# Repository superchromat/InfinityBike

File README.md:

# Infinity Bike

Welcome to the Infinity Bike repository. A simple and inexpensive indoors bike training video game with built-in sensors that allows the player to ride on a virtual track.

Visit our website! www.infinitybike.net

## Why use Infinity Bike? 

Rainy days and the Winter season can really disrupt a training program. Riders always have the option to mount their bike on a trainer but the monotony of trainers
will always make it a bit difficult to keep up the pace. This is why we decided to add a little bit on interactivity to our training program. The Infinity Bike set-up is designed to be a simple as possible
while still allowing a rider to read the speed and steering from a bike mounted on any trainers and relay the information to the computer. 

See the Youtube video (for a deprecated version of Infinity Bike): 

## Where are we in development 
In its current form, the code should compile on a Windows or Mac. We have the communication between Arduino and Unity established and we even have a demo track that you can use to test
your set-up. If you want to take full advantage of this work, you will need to have access to a 3D printer. (Tip : A lot of community libraries are starting to have them available to the public.)
Alternatively, you could design and machine your own parts. If you do, let us know!

## Installation
To participate to this project, start by cloning the repository to a drive on your computer. You should get all the assets for the Unity program in the Infinity Bike folder and the Arduino Code in the ArduiBike folder.
Don't have a bike/trainer or access to a 3D printer? You can easily build a small arduino circuit that fits on your desk. Alternatively, the Arduino inputs can be emulated with the keyboard by
setting a flag in the Unity inspector.

If you make a change you think is worth including in the main project, send us a pull request and we will review it! 

Sadly, we don't have a ready out of the box version yet but it's on the to-do list. For now, you will need to clone the repository and build the current scene for your system.
### Hardware
#### Non 3D Printed parts list

1 x <a href="https://store.arduino.cc/usa/arduino-nano">Arduino nano</a> ($22.00)<br/>
1 x <a href="https://www.amazon.com/Elegoo-6PCS-tie-points-Breadboard-Arduino/dp/B01EV6SBXQ/ref=br_lf_m_d2xh2ecztuwj4fa_img?_encoding=UTF8&s=pc">Mini Breadboard</a> ($1.33/unit)<br/>
1 x <a href="https://www.aliexpress.com/item/100PCS-LOT-1-4W-220-ohm-resistor-1-ROHS1-4w-220R-ohm-Metal-Film-Resistors/32689231347.html?spm=2114.search0104.3.22.6e6347b5Z7ERSI&ws_ab_test=searchweb0_0,searchweb201602_2_10152_10065_10151_10344_10068_10130_5722815_10342_10547_10343_10340_5722915_10548_10341_5722615_10696_10084_10083_10618_10139_10307_5722715_5711215_10059_308_100031_10103_10624_10623_10622_5711315_5722515_10621_10620,searchweb201603_1,ppcSwitch_5&algo_expid=38f3e0b1-dc13-4f86-8131-47538c0df9db-3&algo_pvid=38f3e0b1-dc13-4f86-8131-47538c0df9db&priceBeautifyAB=0">220 Ohm resistor</a> ($1.00/kit)<br/>
1 x <a href="https://www.amazon.com/Uxcell-a15011600ux0235-Linear-Rotary-Potentiometer/dp/B01DKCUVMQ/ref=zg_bs_306810011_1?_encoding=UTF8&psc=1&refRID=ZPQ3XYHZQJXNW7W0AH5P">10K Potentiometer </a> ($1.80/unit)<br/>
1 x <a href="https://www.aliexpress.com/item/KY-003-Standard-Hall-Magnetic-Sensor-Module-Works-with-Arduino-Boards-for-Arduino/32693432353.html?spm=2114.search0104.3.186.599d770dWMU1Zt&ws_ab_test=searchweb0_0,searchweb201602_2_10152_10065_10151_10344_10068_10130_5722815_10342_10547_10343_10340_5722915_10548_10341_5722615_10696_10084_10083_10618_10139_10307_5722715_5711215_10059_308_100031_10103_10624_10623_10622_5711315_5722515_10621_10620,searchweb201603_1,ppcSwitch_5&algo_expid=5d7e9e2e-c6de-4431-8a5b-cecc73fa021c-27&algo_pvid=5d7e9e2e-c6de-4431-8a5b-cecc73fa021c&priceBeautifyAB=0">Hall sensor </a> ($0.96)<br/>
20 cm x <a href="https://www.aliexpress.com/item/5m-lot-GT2-6mm-open-timing-belt-width-6mm-GT2-belt-Rubbr-Fiberglass-cut-to-length/32811832945.html?spm=2114.search0104.3.50.4ca843e4JrNX47&ws_ab_test=searchweb0_0,searchweb201602_2_10152_10065_10151_10344_10068_10130_5722815_10342_10547_10343_10340_5722915_10548_10341_5722615_10696_10084_10083_10618_10139_10307_5722715_5711215_10059_308_100031_10103_10624_10623_10622_5711315_5722515_10621_10620,searchweb201603_1,ppcSwitch_5&algo_expid=1aae0170-0588-45a1-a4ac-2558d64e76cf-7&algo_pvid=1aae0170-0588-45a1-a4ac-2558d64e76cf&priceBeautifyAB=0"> 6 mm 3D printer timing belt </a> ($3.33)<br>
1 kit x <a href="https://www.aliexpress.com/item/Hot-Sale-1-Set-300pcs-M3-304-Stainless-Steel-Hex-Socket-Screws-Bolt-With-Hex-Nuts/32808686142.html?spm=2114.search0104.3.1.703b7491nfv8lT&ws_ab_test=searchweb0_0,searchweb201602_2_10152_10065_10151_10344_10068_10130_5722815_10342_10547_10343_10340_5722915_10548_10341_5722615_10696_10084_10083_10618_10139_10307_5722715_5711215_10059_308_100031_10103_10624_10623_10622_5711315_5722515_10621_10620,searchweb201603_1,ppcSwitch_5&algo_expid=671cbcd2-b8c1-400f-b5f3-cc37f87cfeda-0&algo_pvid=671cbcd2-b8c1-400f-b5f3-cc37f87cfeda&priceBeautifyAB=0">Various Lenght M3 screws and bolts</a> ($6.82)<br/>
1 x <a href= "https://www.aliexpress.com/item/Universal-Magnet-For-Bicycle-Bike-Cycling-Computer-Works-Speedometer-Odometer-Drop-Shipping/32852306956.html?spm=2114.search0104.3.21.32461d8aw5yTQN&ws_ab_test=searchweb0_0,searchweb201602_2_10152_10065_10151_10344_10068_10130_5722815_10342_10547_10343_10340_5722915_10548_10341_5722615_10696_10084_10083_10618_10139_10307_5722715_5711215_10059_308_100031_10103_10624_10623_10622_5711315_5722515_10621_10620,searchweb201603_1,ppcSwitch_5&algo_expid=20a02fd9-cbb1-4fab-92b5-93c50623b4ab-3&algo_pvid=20a02fd9-cbb1-4fab-92b5-93c50623b4ab&priceBeautifyAB=0"> Bicycle speedometer magnet </a> ($0.98) <br/>

** Estimated prices

#### 3D Printed parts list
All the 3D print .stl files are available on [Thingiverse](https://www.thingiverse.com/thing:2933374). The picture below list them all. 
We mounted the material above with 3D printed parts. 
The files we used are listed bellow and they're numbered with the same convention as the image above. 
You can use them as-is but make sure that the dimensions we used match your bike.

##### Parts filename
1. FrameConnection_PotentiometerHolder_U_Holder.stl
2. FrameConnection_Spacer.stl
3. BreadboardFrameHolder.stl
4. Pulley_PotentiometerSide.stl
5. Pot_PulleyConnection.stl
6. FrameConnection.stl
7. Pulley_HandleBarSide_Print2.stl
8. FrameToHallSensorConnector.stl
9. PotHolder.stl
10. HallSensorAttach.stl
##### Assembled parts pictures

Please note that we are currently working on a better stearing measurement device. As seen in the picture above, it is based on a rotation platform placed under the bike wheel. 

More info on this device is available [here](https://github.com/AlexandreDoucet/InfinityBike/tree/master/Ressources/3DprintedParts%20STL%20V0.1/RotationPlatform).

#### Circuit

## How to use?
We published a short 
<a href="https://www.instructables.com/id/Infinity-Bike-Indoors-Bike-Training-Video-Game/">instructable</a> 
tutorial that should provide enough information to get started with this project. 

Please note that this tutorial is no longer up to date with the project and will need to be revisited. Building a more in-depth tutorial for potential contributors is on our To-do list.

** Because we used blender to generate the 3d models, you must have blender installed before opening the project. Otherwise some assets wont load properly.**

## How to contribute? 
From now on, we use the [git branching model proposed by Vincent Driessen](https://nvie.com/posts/a-successful-git-branching-model/). 

To add features to the project, please branch out of the develop branch. The testing of pull request will be done with the 018.3.12f1 version of Unity. 

### Project structure 

### Medium term goals 

## Credits
### Project contributors
Alexandre Doucet (_Doucet_)</br>
Maxime Boudreau (MxBoud)</br>
Alexis Nosovich 

### External ressources
[The Unity game engine](https://unity3d.com)

This project started after we read the tutorial by Allan Zucconi "how to integrate Arduino with Unity" ( https://www.alanzucconi.com/2015/10/07/how-to-integrate-arduino-with-unity/ )

The request from the Arduino are handled using the SerialCommand library ( https://github.com/kroimon/Arduino-SerialCommand )

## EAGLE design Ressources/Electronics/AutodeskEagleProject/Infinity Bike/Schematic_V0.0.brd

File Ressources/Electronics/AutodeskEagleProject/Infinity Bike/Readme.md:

This is the first iteration of a custom PCB for the Infinity bike project.

It has been tested and it works, but some improvement are planned for the next iteration:

-The holes on the PCB are systematically too small.
-We will design places for a few buttons. The main purpose of these buttons would be to enable an in game calibration sequence to make sure the steering behaves as expected.
-The design needs some mounting holes.
-The spacing between the JST connectors needs to be increased.

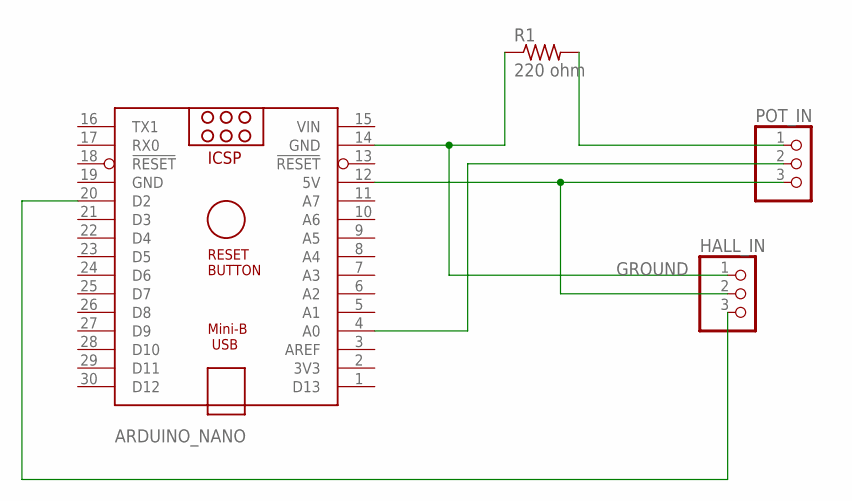
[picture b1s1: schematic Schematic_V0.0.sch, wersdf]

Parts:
ARDUINO_NANO: ARDUINO_NANO
HALL_IN: PINHD-1X3; 1X03
POT_IN: PINHD-1X3; 1X03
R1: 220 ohm; 0204/7

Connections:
GROUND: ARDUINO_NANO.14 (GND), ARDUINO_NANO.19 (GND), HALL_IN.1, R1.1
unnamed: ARDUINO_NANO.12 (5V), HALL_IN.2, POT_IN.3
unnamed: POT_IN.1, R1.2
unnamed: ARDUINO_NANO.4 (A0), POT_IN.2
unnamed: ARDUINO_NANO.20 (D2), HALL_IN.3
VIN: ARDUINO_NANO.15 (VIN)

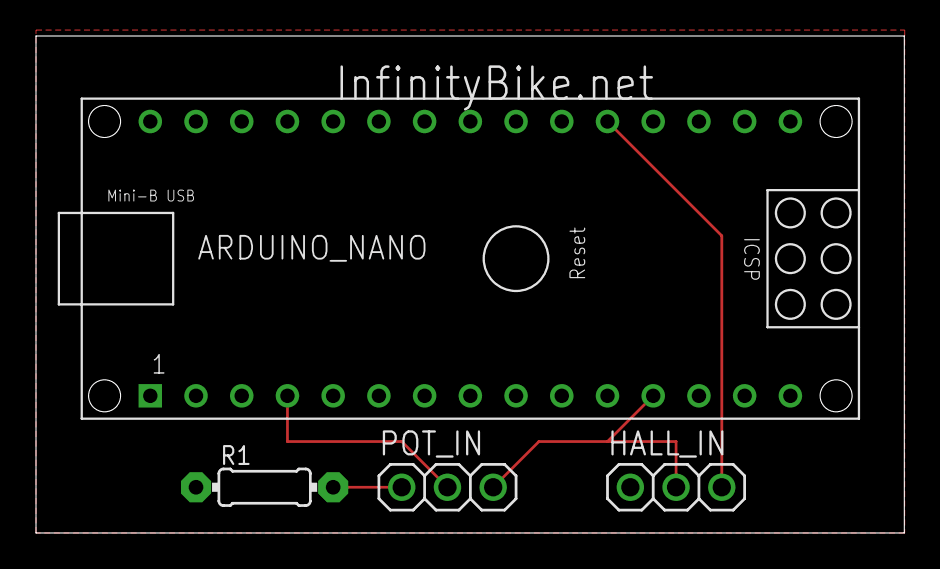
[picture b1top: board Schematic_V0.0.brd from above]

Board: 2 copper layers, 48.2 x 27.6 mm, 4 parts (0 on the bottom side), 5 nets.

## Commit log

2018-05-25 Clean Up
2018-05-25 Initial Unity Commit
2018-05-25 Adding the Unity and Arduino Files
2018-05-25 Unity Assets
2018-05-25 Extra instructable info
2018-05-25 Additionnal Unity Settings
2018-05-26 Added a port auto detection to start communication with the arduino without having to select the comport manually.
2018-05-27 Marginal changes
2018-05-27 Fixed a small bug in SerialCommand.cpp
2018-05-27 Updated ArduinoThread so the AutoDetect works also on macOs
2018-05-27 changes to the README
2018-05-27 Scene cleanups and added a read me.
2018-05-27 Read Me Typos
2018-05-27 Added the logo image
2018-05-27 Updated Logo
2018-05-27 Minor changes
2018-05-27 Minor changes to the Read me.
2018-05-27 Added circuit schematics
2018-05-27 Added Hardware list to ReadMe
2018-05-27 Added some images
2018-05-27 Added the assembled parts picture
2018-05-27 Minor tweaks
2018-05-27 Added instructable hyperlink
2018-05-30 Cleaned up the folders and modified the Respawned tools.
2018-05-31 Tweaked the behaviour of the camera.
2018-06-01 Improved on the bike physics.
2018-06-01 Removed objects from scene that required a prefab to test a missing prefab problem.
2018-06-01 .' git commit -m. git commit -m".
2018-06-02 1. added "NPCs" that spawn on the track and travel with the player. Their speed was set up to match closely the current speed of the player with some added variations to make it feel a bit more natur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
2018-06-03 General clean up of the project folders. Added a few safegards to the EditorRespawNodeSet script to prevent errors is no track node array is selected.
2018-06-03 Added a public variable to change the distance the NPC spawns bebehind the player.
2018-06-03 Fixed a bug where the respawning NPC spawned outside of the track.
2018-06-03 Tweaked the friction on the player to make slowing down smoother.
2018-06-04 Added FOV variability with the speed to improve the feeling of speed.
2018-06-05 prevented spawning ahead of the player by preventing spawning of slower npc.
2018-06-06 Fixed the arduino not connecting but when changing ports, the arduino code must be re uploaded.
2018-06-10 Fixed Arduino Thread so it works if useArduinoPort = false.
2018-06-12 Fixed the auto detect function to properly detect arduino. Added the option to plug, unplug and replug arduino while code is active.
2018-06-13 Refactoring of the arduino thread and player controler.
2018-06-13 Started implementing a level select menue.
2018-06-14 Added new elements and scripts to the start screen to select a button by accelerating on the bike. This should allow the play to navigate menues using only the front wheel angle and the speed of the 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
2018-06-14 Added transparent BG logo
2018-06-15 Added a few tweaks to the arduino code to make the transition between UNO and Nano smoother.
    Changed how the main screen detected the buttons to make it automatic.
    Added an exit application button to the main screen.
2018-06-17 Fixed the main screen softlock if you entered the options menu.
2018-06-18 Implemented self driving AI
2018-06-18 Added a save/load system to the AiSettings.
2018-06-20 added variable AI player
2018-06-20 Made improvements on the track node tools but accidently deleted all the existing nodes :)
2018-06-20 Regenerated the track nodes
2018-06-21 Tweaked the npc initial conditions and player data.
2018-06-22 Fixed track nodes and improve node setting tool
2018-06-22 Added a save/load to the track nodes
2018-07-02 Made significant refactoring to the Arduino Code and eliminated the need to create a new thread thread every time Unity makes a request.
    Added a windows paint startscreen because art is hard.
2018-07-02 You can now navigate the menus. There is still lots of refactoring to do but it's functionnal.
2018-07-02 Added keyboard controls
2018-07-02 Added TerrainBuilderTools
2018-07-02 Updated terrain
2018-07-03 Tweaked the bike physics to reduce gitterness
2018-07-05 Changed the layout and bugproofed the tracknode tool. Added a PID calculation to the AI drivers to help them when they get stuck on a hill.
2018-07-06 Tweaked physics on the bike to try and minimise the rough ride. Improved the loading/saving to display the available tracks in the editor.
2018-07-10 Added more error handling for the arduino thread
2018-07-15 Tweaked the camera to smooth jitter when riding on rough terrain.
2018-07-15 Added keyboard controls via the run arduino thread script.
2018-07-16 Added a respawn option to the menu in the main game.
2018-07-16 Added terrain builder tools prototype.
2018-07-17 Fixed UV maping and added a test track.
2018-07-18 Grammar and typos
    Fixed some grammar errors and typos.
2018-07-18 Added an example of how to use BezierSpline.
2018-07-18 Improved TerrainBuilderTools and created the first loop track with bezier curve...and treesgit add .
2018-07-20 Added Trees (TO MANY OF THEMgit add . )
2018-07-20 Added a loading screen and tweaked the menu system/layout.
2018-07-20 Fixed a merge conflict in the MainGame2 scene
2018-07-23 Added a new texture
2018-07-23 Added a new experimental terrain.
2018-07-26 Improved UI functionalitied and it looks nicer now.
2018-07-27 - Added a save/load feature to the besier spline script. You can access these with a right click on the script in the inspector. - "Fixed" the mesh having a gap at the start when the loop is closed. 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
2018-07-27 Investigated and resolve the bezier points disappearing.
2018-07-27 Adde a temporary soothing to the track so allow testing on it. Currently averages track heights over a few spots in the MeshfromSpline script
2018-08-01 -Made adjustements and fixed to the save/load scripts. -Changed the way the track node tool generates the nodes from the bezier curve. -Fixed the AI drivers to allow for much closer track nodes witho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
2018-08-03 Rearanged folders to allow the project to be build.
2018-08-03 Added the ability to draft behind NPC for a reduced wind resistance.
2018-08-03 AiDriver Optimisations
2018-08-03 Improved performance by refactoring AiDriver and respawn code
2018-08-04 Improved terrain
2018-08-04 Fixed discontinuity at the end of a track loop
2018-08-04 Fixed track discontinuity
2018-08-04 Tweaked the AI driver script
2018-08-04 Made minor fixes to the 3DPlayer Idle state
2018-08-04 Adjusted some features of the MountainViewMap
2018-08-04 Improved AI, AI generator and AI respawning
2018-08-04 Fixed more merge conflicts
2018-08-04 Fixed the velocity not displaying
2018-08-05 Refactored the code for drafting to allow a more modularity with it.
2018-08-05 Updated the current build
2018-08-06 Fixed respawn button not being linked to the player resspawns script.
2018-08-06 Removed duplicate function that called and subscribed to the onRespawn actions
2018-08-07 Simplified the references in the canvas to the player rigidbody by adding a the commonCanvasVariables script to the canvas
2018-08-09 Improved AI performance/spawning scenarios.
2018-08-10 - Improved the AI PID with scripted PID tuner. - Changed drafting mechanics to let the AI match the speed of the player drafting to allow for longer drafting sessions.
2018-08-10 Updated current build
2018-08-10 minor updates to PID values
2018-08-17 Tweaked NPC behaviour to keep the spawning around the player.
2018-10-22 Updated a few scripts and names
2018-10-27 Added the a particule system to the drafting target
2018-11-10 Worked on the 3D models
2018-11-10 Fixed merge conflict
2018-12-16 Implemented a graph system in the game.
2018-12-16 Tweaked when the data should be collected for the graph.
2018-12-30 Improved the cyclist 3d Model
2018-12-30 Added the hidden mac file to .gitignore
2019-01-02 In the process of implementing the 3d model in the main scene.
2019-01-02 Improved the animated cyclist prefab
2019-01-14 Added V0.1 of the rotation detection model.
2019-01-14 Repaired broken link
2019-01-15 adding 3d model on npc
2019-01-15 Improved cyclist animation
2019-01-15 Fixed a wierd but where unity wouln'd link the NPC wheels to the correct entity.
2019-01-17 Fixed a few errors that appeared when the new graphic assets werre added with the mountain view scene. - Also fixed error with the power graph.
2019-01-31 Fixed the menues not appearing properly and the graphs not stoping properly
2019-01-31 Correcting changes that didn't save properly.
2019-01-31 Fixed the data aquisition happening when the player is not moving at the start of the run.
2019-03-31 Improved the responsivenes of the AI when setting the speed.
2019-04-05 Improved arduino code stability, minor tweaks to coding style, improved arduino thread stability on the unity side.
2019-04-06 Fixed current build.
2019-04-07 Adding timeline messages
2019-04-07 Added a temporary workaround so that the auto-connect function is forced to connect to a specific port when the OS is not windows (because the auto connect must be fixed for mac
2019-04-07 Added an optin to inverse to multiply the stearing values by -1 in case of an inverse plugging.
2019-04-07 Created a new scene to implement the EventsNotificationManager script
2019-04-09 Fixed Track node color missing the last node when the number of nodes are uneven.
2019-04-10 Tweaked the respawn mechanic
2019-04-13 Worked on the event features
2019-04-13 Added screenshots
2019-04-13 Changed the 3d printed files folder
2019-04-13 Fixed file name
2019-04-13 Added the Eagle files
2019-04-13 Added pictures
2019-04-13 -Removec unsused files. -Reworked file structe. -Removed duplicate prefabs. -Renamed objects in scenes.
2022-03-17 README2
    Forked this to work on a similiar project.
